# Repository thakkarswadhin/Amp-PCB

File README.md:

Amp-PCB
=======

Amplifier ckt

these are the files for the 1st iteration of the pcb for Sleep Aram project
Made by Anchit Srivastava on eagle

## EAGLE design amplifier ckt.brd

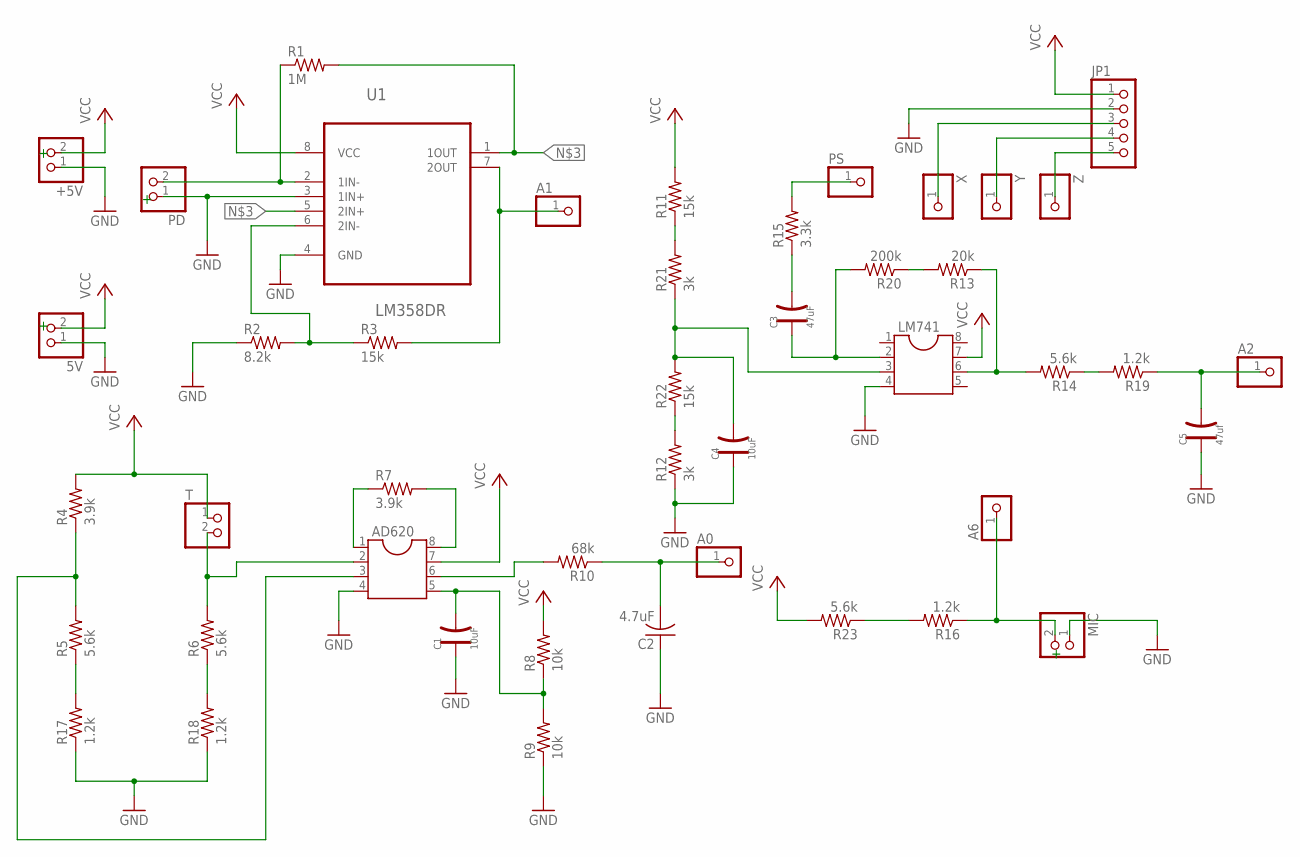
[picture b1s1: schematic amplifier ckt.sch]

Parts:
5V: PINHD-1X2; 1X02
+5V: PINHD-1X2; 1X02
A0, A1, A2, A6: PINHD-1X1; 1X01
AD620: DIL8S; SOCKET-08
C1, C4: 10uF; AVX-B
C2: 4.7uF; C0805
C3: 47uF; AVX-B
C5: 47uf; AVX-B
JP1: PINHD-1X5; 1X05
LM741: DIL8S; SOCKET-08
MIC: PINHD-1X2; 1X02
PD: PINHD-1X2; 1X02
PS: PINHD-1X1; 1X01
R1: 1M; R0603
R2: 8.2k; R0603
R3, R11, R22: 15k; R0603
R4, R7: 3.9k; R0603
R5, R6, R14, R23: 5.6k; R0603
R8, R9: 10k; R0603
R10: 68k; R0603
R12, R21: 3k; R0603
R13: 20k; R0603
R15: 3.3k; R0603
R16, R17, R18, R19: 1.2k; R0603
R20: 200k; R0603
T: PINHD-1X2; 1X02
U1: LM358DR; SOIC127P600X175-8N
X: PINHD-1X1; 1X01
Y: PINHD-1X1; 1X01
Z: PINHD-1X1; 1X01

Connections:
GND: 5V.1, +5V.1, AD620.4, C1.+, C2.1, C4.+, C5.+, JP1.2, LM741.4, MIC.1, PD.1, R2.1, R9.1, R12.1, R17.1, R18.1, U1.3 (1IN+), U1.4 (GND)
unnamed: PD.2, R1.1, U1.2 (1IN-)
unnamed: AD620.5, C1.-, R8.1, R9.2
unnamed: R1.2, U1.1 (1OUT), U1.5 (2IN+)
unnamed: A1.1, R3.2, U1.7 (2OUT)
unnamed: R2.2, R3.1, U1.6 (2IN-)
unnamed: AD620.2, R6.2, T.2
unnamed: R14.1, R19.2
unnamed: AD620.3, R4.1, R5.2
unnamed: AD620.1, R7.1
unnamed: AD620.8, R7.2
unnamed: AD620.6, R10.2
unnamed: A0.1, C2.2, R10.1
unnamed: C4.-, LM741.3, R21.1, R22.2
unnamed: PS.1, R15.2
unnamed: C3.-, R15.1
unnamed: C3.+, LM741.2, R20.2
unnamed: LM741.6, R13.1, R14.2
unnamed: A2.1, C5.-, R19.1
unnamed: A6.1, MIC.2, R16.1
unnamed: R5.1, R17.2
unnamed: R6.1, R18.2
unnamed: R13.2, R20.1
unnamed: R16.2, R23.1
unnamed: R11.1, R21.2
unnamed: R12.2, R22.1
unnamed: JP1.3, X.1
unnamed: JP1.4, Y.1
unnamed: JP1.5, Z.1
VCC: 5V.2, +5V.2, AD620.7, JP1.1, LM741.7, R4.2, R8.2, R11.2, R23.2, T.1, U1.8 (VCC)

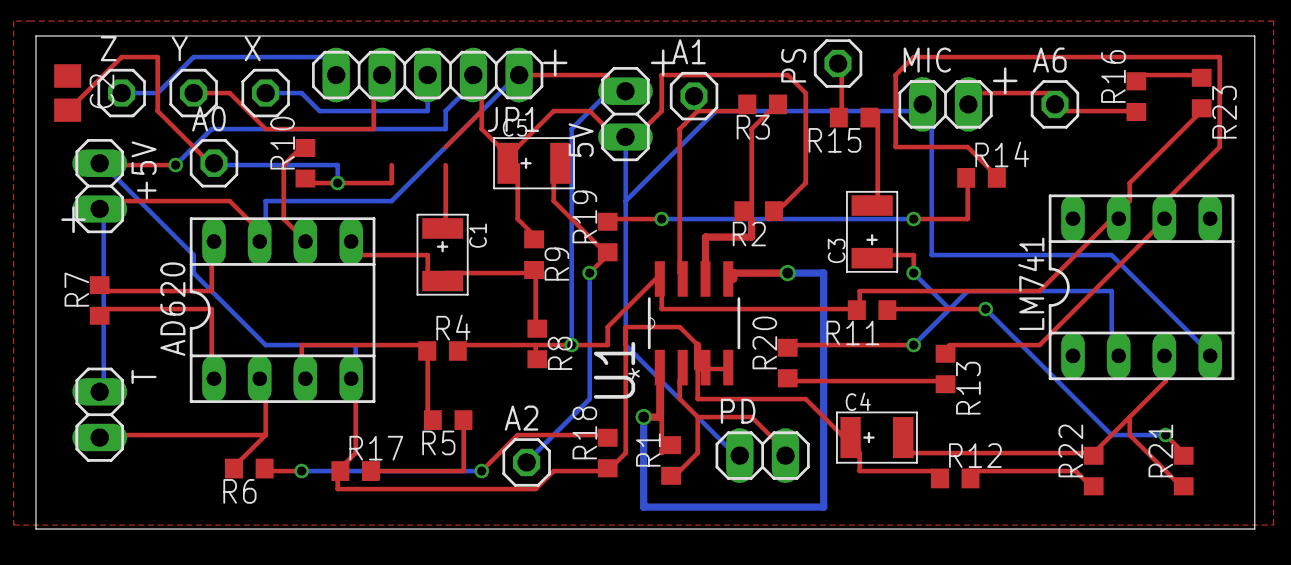
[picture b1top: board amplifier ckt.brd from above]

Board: 2 copper layers, 67.7 x 27.4 mm, 45 parts (0 on the bottom side), 30 nets.

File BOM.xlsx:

Names | SKU |  | Description
LM358DR | 1110010P1 |  | opamp
AD620 | 320070014 |  | 8 pin DIP IC Holder
LM741 | 320070014 |  | 8 pin DIP IC Holder
R1 | 301010151 |  | 1M
R2 | 301010400 |  | 8.2k
R3 | 301010103 |  | 15k
R4 | 301010101 |  | 3.9k
R5 | 301010166 |  | 5.6k
R6 | 301010166 |  | 5.6k
R7 | 301010101 |  | 3.9k
R8 | 301010304 |  | 10k
R9 | 301010304 |  | 10k
R10 | 301010169 |  | 68k
R11 | 301010103 |  | 15k
R12 | 301010170 |  | 3k
R13 | 301010105 |  | 20k
R14 | 301010166 |  | 5.6k
R15 | 301010331 |  | 3.3k
R16 | 301010206 |  | 1.2k
R17 | 301010206 |  | 1.2k
R18 | 301010206 |  | 1.2k
R19 | 301010206 |  | 1.2k
R20 | 301010212 |  | 200k
R21 | 301010170 |  | 3k
R22 | 301010103 |  | 15k
R23 | 301010166 |  | 5.6k
C1 | 0130120P1 |  | 10uF
C2 | 302010146 |  | 4.7uF
C3 | 0130180P1 |  | 47uF
C4 | 0130120P1 |  | 10uF
C5 | 0130180P1 |  | 47uF

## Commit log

2014-10-03 1st iteration of pcb
2014-10-03 added labels
2014-10-07 Bill of materials
2014-10-07 new ckt with header pins
2014-10-07 updated ckt
2014-10-07 final layout
2014-10-08 gerber files
